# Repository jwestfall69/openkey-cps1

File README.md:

# openkey-cps1
---
* [Overview](#overview)
* [Project Status](#project-status)
* [Supported C Boards](#supported-c-boards)
* [CPS 1 Case](#cps-1-case)
* [Supported Games / B-XX Chips](#supported-games--b-xx-chips)
  * [CPS 1](#cps-1)
  * [CPS 1.5](#cps-15)
  * [B-XX](#b-xx)
* [Hardware](#hardware)
  * [PCB Manufacturing](#pcb-manufacturing)
  * [BOM](#bom)
  * [Assembly](#assembly)
    * [CPS 1](#cps-1-1)
    * [CPS 1.5](#cps-15-1)
* [Programming](#programming)
  * [Hardware](#hardware-1)
  * [Software](#software)
* [Installation](#installation)
  * [CPS 1](#cps-1-2)
  * [CPS 1.5](#cps-15-2)
  * [Reset Header (optional)](#reset-header-optional)
    * [Reset Capacitor Locations](#reset-capacitor-locations)
    * [Reset Signal Locations](#reset-signal-locations)
    * [Reset Cable](#reset-cable)
    * [Reset Delay Jumper](#reset-delay-jumper)
* [Reverting a modified C Board](#reverting-a-modified-c-board)

## Overview
This is an open source/hardware implementation of an on the fly CPS B-21 chip programmer that consists of a PCB that sits between CPS1/1.5 B and C boards.

Installed:<br>

This project is providing the same functionality as [Undamned's InfiniKey-CPS1](https://www.arcade-projects.com/threads/infinikey-cps1.8337/).  The lack of supply is what prompted me to make openkey-cps1.  If they ever end up coming back in stock please consider purchasing those to support [Undamned](https://www.arcade-projects.com/forums/temple-of-the-undamned.77/)'s work.

Details on *how* to program the CPS B-21 chip configuration can be found in [Eduardo Cruz](http://arcadehacker.blogspot.com/)'s [write up](http://arcadehacker.blogspot.com/2015/04/capcom-cps1-part-1.html) and [youtube video](https://www.youtube.com/watch?v=IBZc__9sM28).  Additional information is also comes from [cps2-reverse](https://gitlab.com/loic.petit/cps2-reverse) project which has details on the [CPS B-21](https://gitlab.com/loic.petit/cps2-reverse/-/tree/master/DLs/DL-0921) chip.

Details on *what* to program can be found in MAME's code for the [CPS1](https://github.com/mamedev/mame/blob/master/src/mame/capcom/cps1_v.cpp#L470).

## Project Status
**PCB:** Done

**Firmware:** Need to get untested games tested

**Documentation:** Done

## Supported C Boards
The following unmodified C Boards are supported

* [90630C-4](https://www.mvs-scans.com/index.php/CPS1_-_C_Board_90630C-4)
* [90631C-5](https://www.mvs-scans.com/index.php/CPS1_-_C_Board_90631C-5)
* [92641C-1](https://www.mvs-scans.com/index.php/CPS1_-_C_Board_92641C-1)

## CPS 1 Case
openkey-cps1 will not fit in the CPS 1 case.  As far as I know only Varith and Capcom World 2 came in a case.  You can still use openkey-cps1 to desuicide the C board.  Replace the battery then boot up the game with openkey-cps1 installed.  Verify it runs as expected, then power off, remove openkey-cps1 and reinstall the board in the case.

## Supported Games / B-XX Chips
openkey-cps1 supports either having a 5 position switch or using solder jumpers for picking what to program into the B-21 Chip.  For the switch, ensure the switches are fully set.  You should hear a click sound as you change the position.

 Below is a list of supported configurations/games and what switches/jumpers must be used for each.

### CPS 1
| Switch<br>12345 | Program ROM Labels | Game Name | Tested / Working |
|:---------------:|:------------------:|-----------|:--------------:|
| 00000 | CCE<br>CCJ<br>CCU<br> | Captain Commando | YES |
| 00001 | KDE<br>KDJ<br>KDU | The King of Dragons | |
| 00010 | KR_23E<br>KR_23J<br>KR_23U | Knights of the Round | YES |
| 00011 | Q5 | Capcom World 2 | YES |
| 00100 | QDU | Quiz & Dragons | YES |
| 00101 | RTE<br>RTJ<br>RTU | Three Wonders | YES |
| 00110 | VAE<br>VAJ<br>VAU | Varth | YES |

### CPS 1.5
| Switch<br>12345 | Program ROM Labels | Game Name | Tested / Working |
|:---------------:|:------------------:|-----------|:--------------:|
| 00111 | CDE<br>CDJ<br>CDT<br>CDU | Cadillacs & Dinosaurs | YES |
| 01000 | MBE<br>MBJ<br>MBU | Slam Masters / Muscle Bomber | YES |
| 01001 | MBDE<br>MBDJ | Muscle Bomber Duo | |
| 01010 | PSE<br>PSH<br>PSJ<br>PSU | Punisher | YES |
| 01011 | TK2E<br>TK2J<br>TK2U | Warriors of Fate | |

### B-XX
For B-XX chips prior to B-21 the configurations were hard coded into the chip.  Its possible to program the B-21 to mimic these older chips.

Some older B-XX boards will have the number stamped on instead of etched into the chip.  These stamped numbers maybe incorrect.  For example I have a final fight board that has 04 stamped on as the XX number.  Picking B-04 on openkey-cps1 didn't work.  After dumping the program roms I was able to determine it was the ffightua romset.   [Mame](https://github.com/mamedev/mame/blob/master/src/mame/capcom/cps1_v.cpp#L1754) shows this romset actually uses B-01.  Switching to B-01 made the game work.

| Switch<br>12345 |  B-XX  | Tested / Working |
|:---:|:------:|:---------------:|
| 01100 | B-01 | YES |
| 01101 | B-02 | |
| 01110 | B-03 | |
| 01111 | B-04 | YES |
| 10000 | B-05 | |
| 10001 | B-11 | YES |
| 10010 | B-12 | YES |
| 10011 | B-13 | YES |
| 10100 | B-14 | YES |
| 10101 | B-15 | |
| 10110 | B-16 | YES |
| 10111 | B-17 | YES |
| 11000 | B-18 | |
| 11001 | B-21 | YES |

## Hardware
### PCB Manufacturing
There are no special requirements for manufacturing.

I've been using [jlcpcb](https://jlcpcb.com/) for PCB manufacturing.  Just watch out that by default they will add an order number to the silk screen unless you tell them not to.

### BOM
| Quantity | Description | Part Number | DigiKey | Mouser | Notes |
|:----------:|-------------|-------------|---------|--------|-------|
| 1 | ATtiny404 20Mhz | ATTINY404-SSN | [ATTINY404-SSN-ND](https://www.digikey.com/en/products/detail/microchip-technology/ATTINY404-SSN/9947546) | [556-ATTINY404-SSNR](https://www.mouser.com/ProductDetail/Microchip-Technology-Atmel/ATTINY404-SSNR?qs=F5EMLAvA7IAEqD7Aw0z%252B9Q%3D%3D) | Other ATtiny tinyAVR 0/1/2-series models should be viable as well.  The code compiles to just under 1.5K in size, so any that have 2k or more of flash should work.  Just note I have only tested with 404s |
| 1 | 100nf / 0.1uf SMD Ceramic Capacitor 0805 Size | | | | |
| 1 | 5 Position Slide Switch | Würth Elektronik 416131160805 | [732-3855-2-ND](https://www.digikey.com/en/products/detail/w%C3%BCrth-elektronik/416131160805/3174531) | [710-416131160805](https://www.mouser.com/ProductDetail/Wurth-Elektronik/416131160805?qs=2kOmHSv6VfT1rqUsojuQog%3D%3D) | **Optional** not needed if using the solder jumpers to pick the game.
| 4 | CPS1: 2x20 Pin Male IDC connector<br>CPS1.5: 2x20pin Male Header (no shroud) | SBH11-PBPC-D20-ST-BK<br>N/A | [S9175-ND](https://www.digikey.com/en/products/detail/sullins-connector-solutions/SBH11-PBPC-D20-ST-BK/1990068)<br>[2x20 Pin Header](https://www.amazon.com/dp/B083DYVWDN?psc=1&ref=ppx_yo2ov_dt_b_product_details) | ?? | This is just a standard IDE male connector<br>This is just a normal 2x20 Pin header you might find for a PI's GPIO pins |
| 4 | 2x20 Pin Female socket | SFH11-PBPC-D20-ST-BK | [S9200-ND](https://www.digikey.com/en/products/detail/sullins-connector-solutions/SFH11-PBPC-D20-ST-BK/1990093) | ?? |  |

**IMPORTANT** For the 2x20 Pin Female socket, if you choose a different part, make sure you get ones that have the extra plastic on the edge as seen below.

The extra plastic prevents the connector from being inserted off-by-one.  An off-by-one insertion will cause a direct short to ground. This can cause catastrophic damage to your Game PCB if your power supply doesn't have short circuit protection.

Don't be fooled into thinking you don't need the extra plastic because you see the key. The bottom connector for example is too skinny for the key to actually prevent off-by-one insertion.  Ask me how I know ;)

### Assembly
#### CPS 1
Nothing special is needed when assembling a openkey-cps1 that will be used in a normal non-case'd CPS1 board.  Install SMD components first, then install the 40 pin male/female connectors.

#### CPS 1.5
Installing openkey-cps1 in a CPS 1.5 case is a tight fit height wise.  The pins that stick out of the C board are at the point of touching the top of the case.  If you are ok with this just use the 40 pin IDE style connectors.  Otherwise you can do the following.

To deal with this the best course of action is to only have raw pins for the male 40 pin connectors instead of ones with the plastic shroud.  This will allow the C board to sit flush with the openkey-cps1 board and reduce the height enough to not touch the top of the case.  Below is what has worked well for me, but there maybe better ways.

Some things to consider:
  * The normal pin length of a male pin is 6mm
  * The max pin height above the openkey-cps1 board should **not exceed 7mm**.  Any longer and the pin will bottom out on the female connector on the C Board.  This will cause the C board to not sit flush to the openkey-cps1 board and defeat the purpose of using raw pins.
  * You can't just install the normal 40pin IDE style connector then remove the shroud.  The resulting pin length ends up being 8mm.
  * You can't just install a normal 40 pin header and remove the plastic.  The resulting pin length ends up being 8mm.
  * The total length of metal pin on most headers is going to be 11.5mm
  * PCB thickness should be 1.6mm, which leave about 10mm worth of metal pin length we must deal with.

This method targets having 7mm above and 3mm below the openkey-cps1 board.  I've tried 6mm/4mm, but that 4mm is long enough there is risk it could hit/damage components on the B board.

You will want 4 normal 2x20 pin headers where the total metal length is 11.5mm.  Additionally you will want something you can use as a 1.5mm spacer.  I'm using the 2 black 24AWG wires in the picture below.

You will want to install 2 of the 2x20 pin header upside into board.  I would advise doing the 2 outer ones first. Put the 1.5mm spacer between the board and the plastic part of the connector as seen below.

Now flip the board over to the side we will be soldering.  It should look something like this.  

The length of the pins should be 3mm, which will mean 7mm on the top.

At this point I would tack 2 pins on each connector then verify spacing of the connectors looks good.  It should look something like this (with the spacer wires removed)

If you measure the pin lengths they should be right at 7mm.

Fully solder those 2 connectors.  Its extra importing you check your soldering that this point.  The next steps will involve removing the plastic part of the connectors which will make every pin independent and a pita to solder.

To protect the board I would put down some painters tape.  Additionally I use this [chip lifter](https://www.amazon.com/Wiha-27921-PicoFinish-Precision-Chiplifter/dp/B0875LSTD3/ref=sr_1_5)  as my pry tool. The grove makes it possible to get in between the pins to when prying up the plastic.

If you have a hot air station you can use it to heat (200C) up the plastic to make it easier to get off.  You will want to do the removable in a couple passes with your pry tool, lifting up the plastic a few mm per pass.

As you get the plastic higher up on the pins it can be helpful to add a spacer under you pry tool.  I'm just using a old prototype board.

Once you get both plastics off it should looks like this

Then you can go onto the middle 2 connectors.  You can bypass using the 1.5mm spacer on these.  Instead just put the connects in the PCB upside down as before, then flip PCB over as if you were going to solder them.  The already soldered connectors will hold the PCB 7mm off your table, which will mean your to be installed connectors will also be 7mm off your table.  Tack, verify and then fully solder.

Repeat the process to remove the plastic

When you are all done you should have this

Now do a test fit of the C board and it should be flush with the openkey-cps1 PCB

Install the SMD components and female 40 pin connectors.  This one was going on my Punisher board, so I just used the solder jumpers instead of installing the 5 position switch.

## Programming
The latest firmware will work on both revisions of openkey-cps1 hardware.

### Hardware
Programming is done with a UPDI programmer.  I've been using this one:

[Serial UPDI Programmer for ATmega 0-Series, or ATtiny 0-Series or 1-Series, or AVR DA or AVR DB](https://www.amazon.com/dp/B09X64YRLD?psc=1&ref=ppx_yo2ov_dt_b_product_details)

Note: This programmer (and likely others) has a switch for 3.3V and 5V.  Set it to 5V.

The openkey-cps1 programming port is setup so you can wedge the pins from the above programmer directly into them to programming.

Of course be sure you properly orient the board so the labeled pin/holes match up.  vcc to vcc, gnd to gnd, and updi to updi.

### Software
For software I've been using the [Arduino IDE](https://www.arduino.cc/en/software/) with [megaTinyCore](https://github.com/SpenceKonde/megaTinyCore), which adds support for tinyAVR 0/1/2-Series MCUs.

To install the megaTinyCore you, should just need to add http://drazzy.com/package_drazzy.com_index.json to "Additional Boards Manager URLs" in the settings for the Arduino IDE.

From there you need to configure the board/programming settings.  I've been using these:

**NOTE:** The "Startup Time" was adjusted from my previous picture of the settings, from 0ms to 1ms.  In testing I found when using a 0ms startup there is a small chance the ATtiny won't even execute any code.

## Installation
### CPS 1
Nothing really special here.  Use the dip switches or solder jumpers to pick your game/chip and put the openkey-cps1 board between your C and B boards.  The male/female connectors should prevent you from installing incorrectly.

### CPS 1.5
This is assuming you are using an openkey-cps1 board with the raw pin headers on top.  There is nothing preventing you from install the C board incorrectly.

Use the dip switches or solder jumpers to pick your game.

Verify you have the C board oriented the correct way as seen below.

The C board female connector will prevent you from installing it to high or low, but it will not prevent installation to the left or the right by one.

Check both sides of the female C board connector to verify you dont see any of the pins.

other side

If its off by one of the sides will look like this

### Reset Header (optional)
In openkey-cps1 hardware revision 2025-10-18 an optional reset header was added to allow hooking up openkey to the reset line of the A board.  Its **unlikley** you would need this and I would avoid using it.

Openkey-cps1 is dependent on being able to re-program on the B-21 chip while the cps1 board is in reset.  This is because 2 of the pins related to programming are part of the data bus used by the main CPU to talk to the B-21 chip.  If openkey-cps1 were to try and do any of its programming outside of reset it would cause a bus conflict with the main CPU also trying to use those 2 pins and programming will fail.

#### Reset Capacitor Locations
The length of time the cps1 board is in reset is highly dependent on the reset capacitor located on the A board.  If this capacitor is faulty or going bad it can greatly reduce the amount of time the board is in reset when power is applied.  Before trying to use the reset header on the openkey-cps1 I would first try replacing the reset capacitor.

**Long A Board:**<br>

**Short A Board:**<br>

On both boards its a 1uf/16V ceramic capacitor (higher voltages are ok).

#### Reset Signal Locations
The location provided for each A board type is a through hole.  I would advise installing a right angle header instead of directly soldering a wire.  This will make it easy to connect/disconnect the cable both on the A board and openkey-cps1.

**Long A Board:**<br>

**Long A Board Installed:**<br>

**Short A Board:**<br>

**Short A Board Installed:**<br>

#### Reset Cable
Once you've added the reset header on the A board, run a cable from it to pin 1 on the reset header of the openkey-cps1 as shown below.

Then install the C board onto openkey-cps1 as you normally would.

#### Reset Delay Jumper
With the reset cable hooked up, openkey-cps1 will hold the cps1 board in reset while its programming, then release when complete.  Pins 2 and 3 of the reset header on openkey-cps1 are a jumper that will cause openkey-cps1 to keep the cps1 board in reset longer.  When jumped the firmware will hold the cps1 board in reset for 1 second before and after programming.

**IMPORTANT**: If this jumper is jumped and the reset cable is not hooked up, programming will fail 100% of the time!

## Reverting a modified C Board
Its pretty common to find one of the required C boards as having been modified to disable using the programmable configuration.  This forces them to use their default configuration.

The tale tale sign of a modified C board are pins 45 and 46 will have cut traces (normally they go to ground) and a wire from them to some point on the C board that is supplying 5 volts.  For example

The way I normally revert them is to remove the wire, and then put a solder blob so that pins 45, 46, and 47 (ground) are bridged together.  This puts the board back in its original state with all 3 of those pins being tied to ground.

Here is a close up of the solder blob on the pins

You can also see where they had cut the traces for pins 45 and 46, which would normally connect to that ground plane to the right.

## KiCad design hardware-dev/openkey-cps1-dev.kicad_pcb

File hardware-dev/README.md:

# openkey-cps1-dev Hardware
This is a dev version of openkey-cps1 hardware that makes it possible to rapidly test firmware changes.  I'm mainly just including this in the repo so I don't use it.

**Top:**

**Bottom:**

As you can see its a bit taller then the non-dev version to allow being able to change the selected game and re-program the firmware while the board is plugged into a cps1 A-B-C stack.  The 2 diodes ensure that USB power can only goto the ATtiny and that cps1 board power doesn't goto the USB.

After programming the ATtiny you will want to disconnect it from USB and either power-on or powercycle the cps1 board.  This is to ensure power is fully removed from the ATtiny so it will boot up normally when cps1 power is applied.

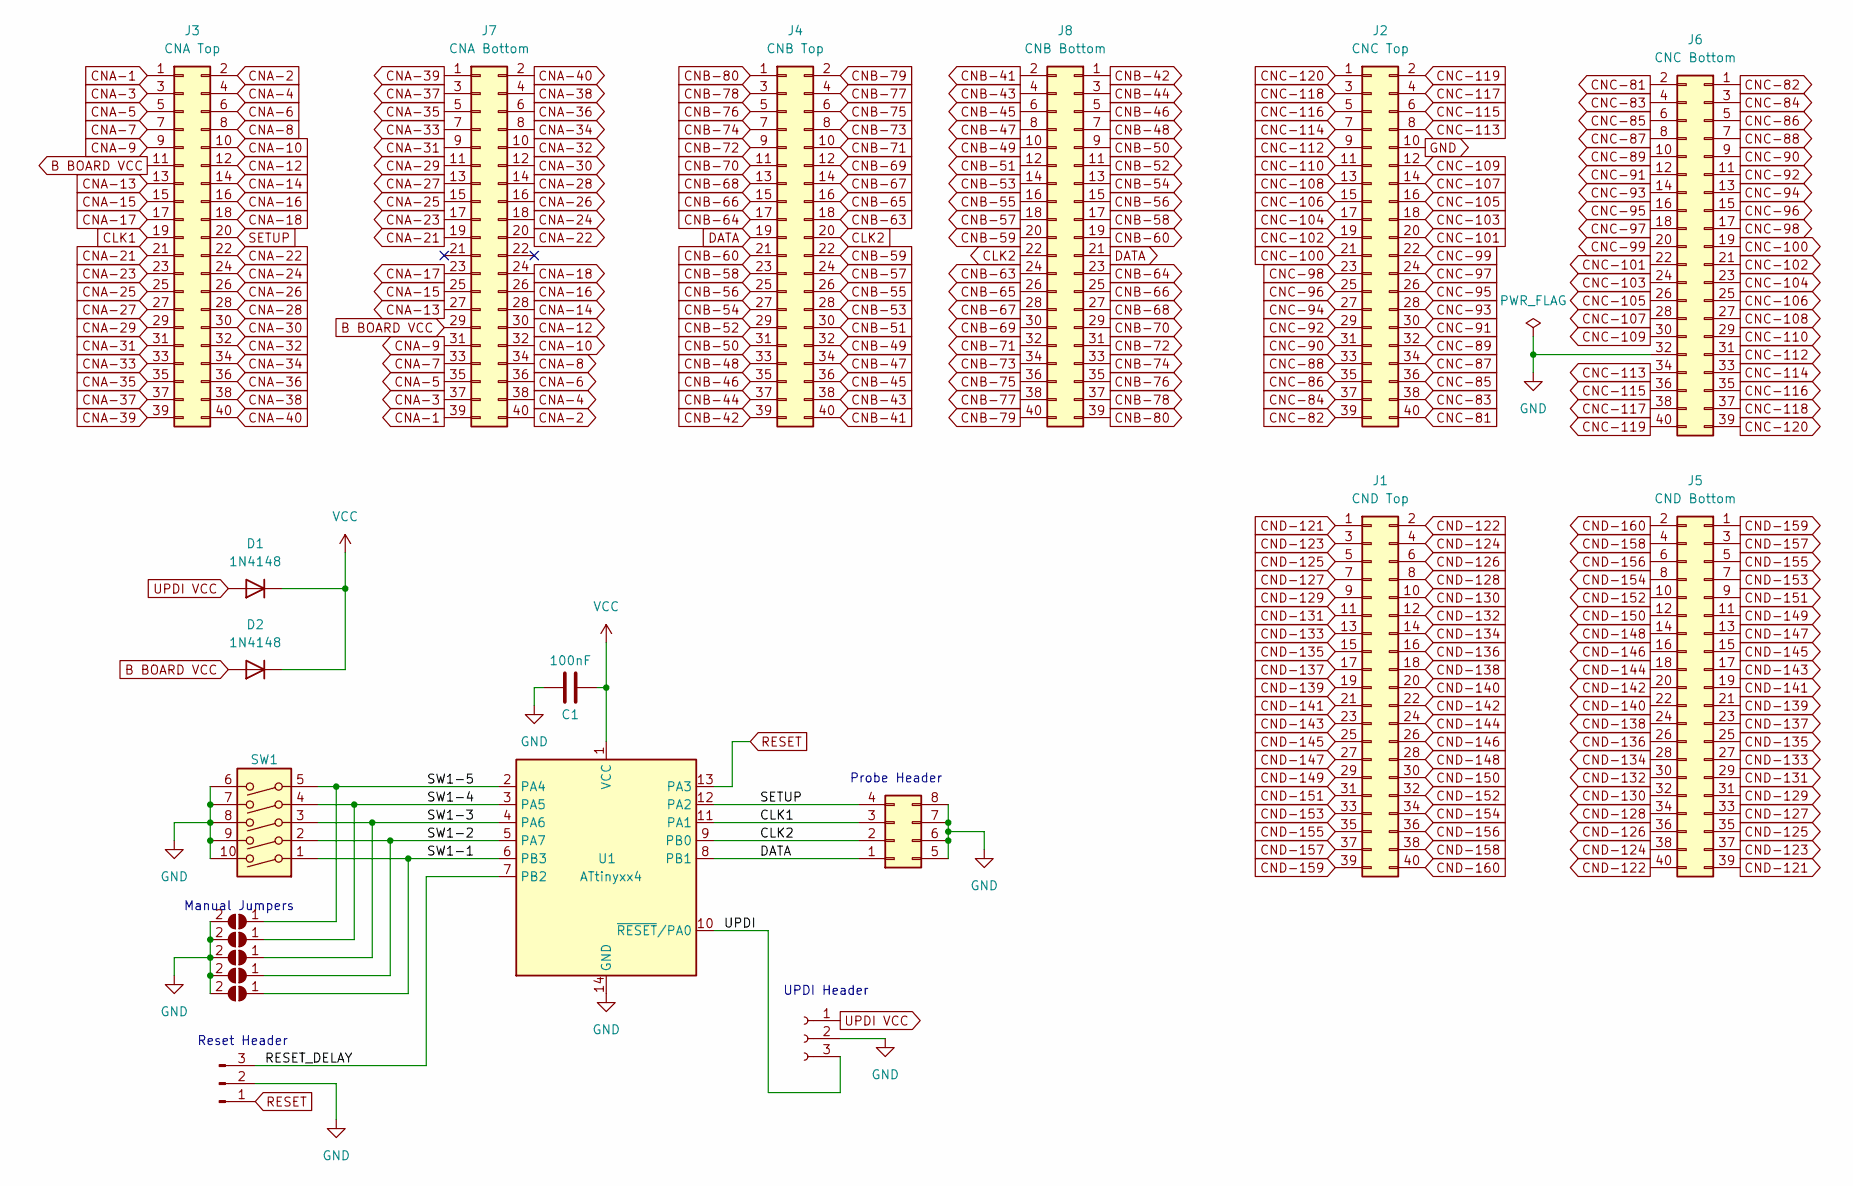
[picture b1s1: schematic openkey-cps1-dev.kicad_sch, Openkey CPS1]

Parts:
C1: 100nF; C_0805_2012Metric_Pad1.18x1.45mm_HandSolder
D1, D2: 1N4148; D_DO-35_SOD27_P7.62mm_Horizontal
J1: CND Top; IDC-Header_2x20_P2.54mm_Vertical_1.3mm
J2: CNC Top; IDC-Header_2x20_P2.54mm_Vertical_1.3mm
J3: CNA Top; IDC-Header_2x20_P2.54mm_Vertical_1.3mm
J4: CNB Top; IDC-Header_2x20_P2.54mm_Vertical_1.3mm
J5: CND Bottom; PinSocket_2x20_P2.54mm_Vertical_1.3mm
J6: CNC Bottom; PinSocket_2x20_P2.54mm_Vertical_1.3mm
J7: CNA Bottom; PinSocket_2x20_P2.54mm_Vertical_1.3mm
J8: CNB Bottom; PinSocket_2x20_P2.54mm_Vertical_1.3mm
J9: Conn_01x03_Female; PinHeader_1x03_P2.54mm_Vertical
J10: Conn_02x04_Top_Bottom; PinHeader_2x04_P2.54mm_Vertical
J12: Conn_01x03_Pin; PinHeader_1x03_P2.54mm_Vertical
JP1, JP2, JP3, JP4, JP5: SolderJumper_2_Open; SolderJumper-2_P1.3mm_Open_Pad1.0x0.6mm
SW1: SW_DIP_x05; SW_DIP_SPSTx05_Slide_Wurth_416131160805_W7.62mm_P1.27mm
U1: ATtinyxx4; SOIC-14_3.9x8.7mm_P1.27mm

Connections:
/RESET_DELAY: J12.3, U1.7 (PB2)
/SW1-1: JP5.1 (A), SW1.1, U1.6 (PB3)
/SW1-2: JP4.1 (A), SW1.2, U1.5 (PA7)
/SW1-3: JP3.1 (A), SW1.3, U1.4 (PA6)
/SW1-4: JP2.1 (A), SW1.4, U1.3 (PA5)
/SW1-5: JP1.1 (A), SW1.5, U1.2 (PA4)
/UPDI: J9.3, U1.10 (~RESET/PA0)
B BOARD VCC: D2.2 (A), J3.11, J7.29
CLK1: J3.19, J10.3, U1.11 (PA1)
CLK2: J4.20, J8.22, J10.2, U1.9 (PB0)
CNA-1: J3.1, J7.39
CNA-2: J3.2, J7.40
CNA-3: J3.3, J7.37
CNA-4: J3.4, J7.38
CNA-5: J3.5, J7.35
CNA-6: J3.6, J7.36
CNA-7: J3.7, J7.33
CNA-8: J3.8, J7.34
CNA-9: J3.9, J7.31
CNA-10: J3.10, J7.32
CNA-12: J3.12, J7.30
CNA-13: J3.13, J7.27
CNA-14: J3.14, J7.28
CNA-15: J3.15, J7.25
CNA-16: J3.16, J7.26
CNA-17: J3.17, J7.23
CNA-18: J3.18, J7.24
CNA-21: J3.21, J7.19
CNA-22: J3.22, J7.20
CNA-23: J3.23, J7.17
CNA-24: J3.24, J7.18
CNA-25: J3.25, J7.15
CNA-26: J3.26, J7.16
CNA-27: J3.27, J7.13
CNA-28: J3.28, J7.14
CNA-29: J3.29, J7.11
CNA-30: J3.30, J7.12
CNA-31: J3.31, J7.9
CNA-32: J3.32, J7.10
CNA-33: J3.33, J7.7
CNA-34: J3.34, J7.8
CNA-35: J3.35, J7.5
CNA-36: J3.36, J7.6
CNA-37: J3.37, J7.3
CNA-38: J3.38, J7.4
CNA-39: J3.39, J7.1
CNA-40: J3.40, J7.2
CNB-41: J4.40, J8.2
CNB-42: J4.39, J8.1
CNB-43: J4.38, J8.4
CNB-44: J4.37, J8.3
CNB-45: J4.36, J8.6
CNB-46: J4.35, J8.5
CNB-47: J4.34, J8.8
CNB-48: J4.33, J8.7
CNB-49: J4.32, J8.10
CNB-50: J4.31, J8.9
CNB-51: J4.30, J8.12
CNB-52: J4.29, J8.11
CNB-53: J4.28, J8.14
CNB-54: J4.27, J8.13
CNB-55: J4.26, J8.16
CNB-56: J4.25, J8.15
CNB-57: J4.24, J8.18
CNB-58: J4.23, J8.17
CNB-59: J4.22, J8.20
CNB-60: J4.21, J8.19
CNB-63: J4.18, J8.24
CNB-64: J4.17, J8.23
CNB-65: J4.16, J8.26
CNB-66: J4.15, J8.25
CNB-67: J4.14, J8.28
CNB-68: J4.13, J8.27
CNB-69: J4.12, J8.30
CNB-70: J4.11, J8.29
CNB-71: J4.10, J8.32
CNB-72: J4.9, J8.31
CNB-73: J4.8, J8.34
CNB-74: J4.7, J8.33
CNB-75: J4.6, J8.36
CNB-76: J4.5, J8.35
CNB-77: J4.4, J8.38
CNB-78: J4.3, J8.37
CNB-79: J4.2, J8.40
CNB-80: J4.1, J8.39
CNC-81: J2.40, J6.2
CNC-82: J2.39, J6.1
CNC-83: J2.38, J6.4
CNC-84: J2.37, J6.3
CNC-85: J2.36, J6.6
CNC-86: J2.35, J6.5
CNC-87: J2.34, J6.8
CNC-88: J2.33, J6.7
CNC-89: J2.32, J6.10
CNC-90: J2.31, J6.9
CNC-91: J2.30, J6.12
CNC-92: J2.29, J6.11
CNC-93: J2.28, J6.14
CNC-94: J2.27, J6.13
CNC-95: J2.26, J6.16
CNC-96: J2.25, J6.15
CNC-97: J2.24, J6.18
CNC-98: J2.23, J6.17
CNC-99: J2.22, J6.20
CNC-100: J2.21, J6.19
CNC-101: J2.20, J6.22
CNC-102: J2.19, J6.21
CNC-103: J2.18, J6.24
CNC-104: J2.17, J6.23
CNC-105: J2.16, J6.26
CNC-106: J2.15, J6.25
CNC-107: J2.14, J6.28
CNC-108: J2.13, J6.27
CNC-109: J2.12, J6.30
CNC-110: J2.11, J6.29
CNC-112: J2.9, J6.31
CNC-113: J2.8, J6.34
CNC-114: J2.7, J6.33
CNC-115: J2.6, J6.36
CNC-116: J2.5, J6.35
CNC-117: J2.4, J6.38
CNC-118: J2.3, J6.37
CNC-119: J2.2, J6.40
CNC-120: J2.1, J6.39
CND-121: J1.1, J5.39
CND-122: J1.2, J5.40
CND-123: J1.3, J5.37
CND-124: J1.4, J5.38
CND-125: J1.5, J5.35
CND-126: J1.6, J5.36
CND-127: J1.7, J5.33
CND-128: J1.8, J5.34
CND-129: J1.9, J5.31
CND-130: J1.10, J5.32
CND-131: J1.11, J5.29
CND-132: J1.12, J5.30
CND-133: J1.13, J5.27
CND-134: J1.14, J5.28
CND-135: J1.15, J5.25
CND-136: J1.16, J5.26
CND-137: J1.17, J5.23
CND-138: J1.18, J5.24
CND-139: J1.19, J5.21
CND-140: J1.20, J5.22
CND-141: J1.21, J5.19
CND-142: J1.22, J5.20
CND-143: J1.23, J5.17
CND-144: J1.24, J5.18
CND-145: J1.25, J5.15
CND-146: J1.26, J5.16
CND-147: J1.27, J5.13
CND-148: J1.28, J5.14
CND-149: J1.29, J5.11
CND-150: J1.30, J5.12
CND-151: J1.31, J5.9
CND-152: J1.32, J5.10
CND-153: J1.33, J5.7
CND-154: J1.34, J5.8
CND-155: J1.35, J5.5
CND-156: J1.36, J5.6
CND-157: J1.37, J5.3
CND-158: J1.38, J5.4
CND-159: J1.39, J5.1
CND-160: J1.40, J5.2
DATA: J4.19, J8.21, J10.1, U1.8 (PB1)
GND: C1.1, J2.10, J6.32, J9.2, J10.5, J10.6, J10.7, J10.8, J12.2, JP1.2 (B), JP2.2 (B), JP3.2 (B), JP4.2 (B), JP5.2 (B), SW1.6, SW1.7, SW1.8, SW1.9, SW1.10, U1.14 (GND)
RESET: J12.1, U1.13 (PA3)
SETUP: J3.20, J10.4, U1.12 (PA2)
UPDI VCC: D1.2 (A), J9.1
VCC: C1.2, D1.1 (K), D2.1 (K), U1.1 (VCC)

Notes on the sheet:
UPDI Header
Reset Header
Probe Header
Manual Jumpers

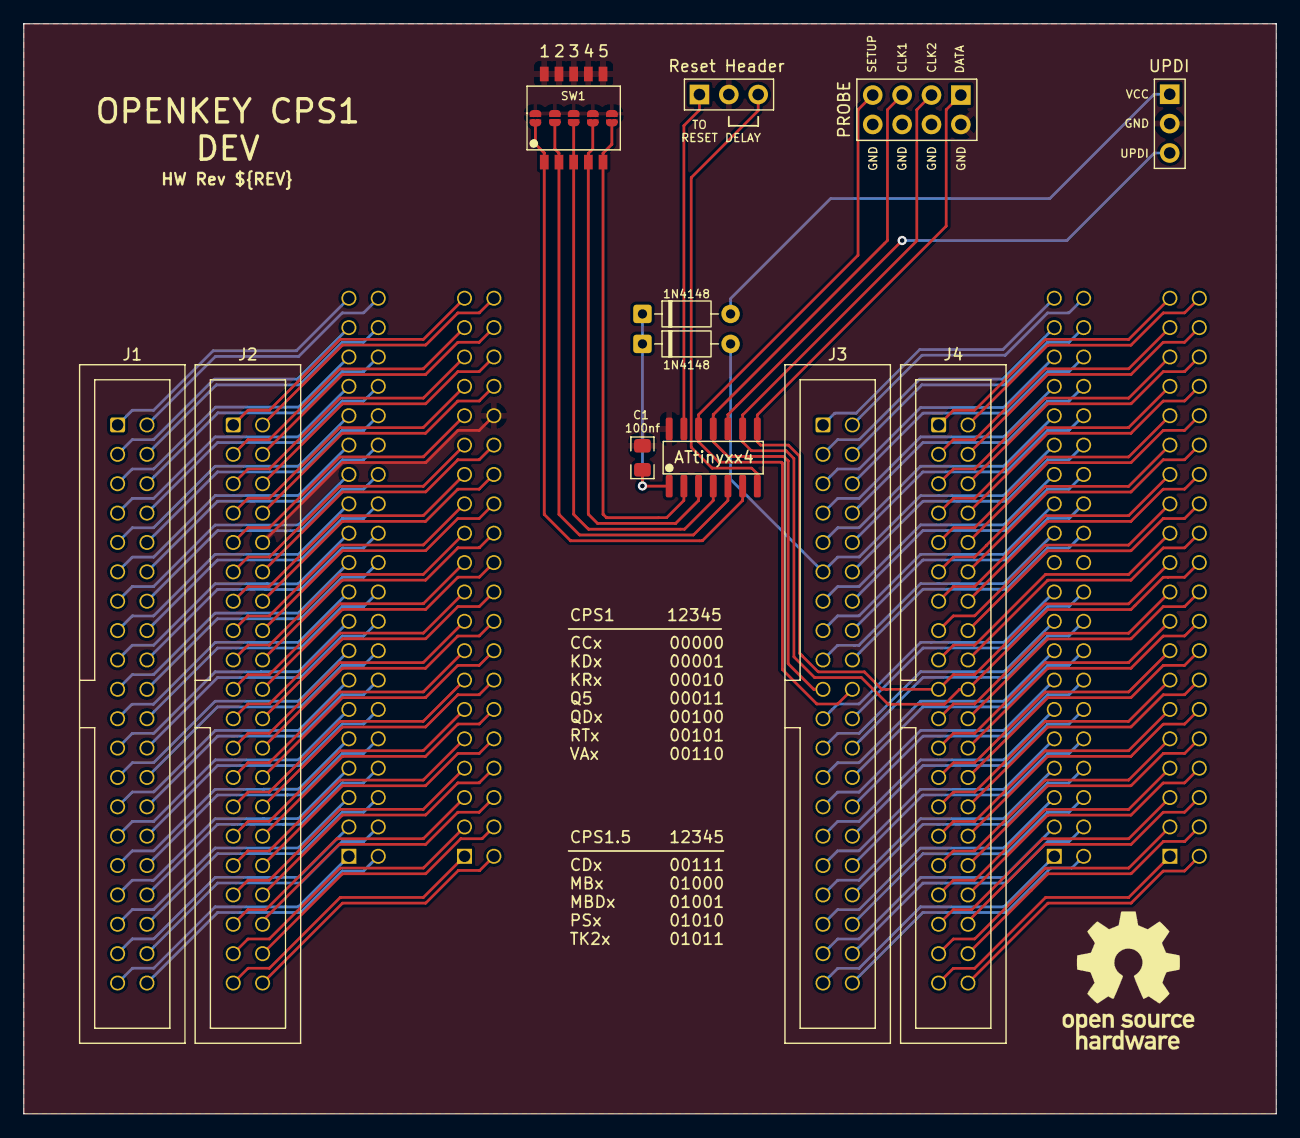
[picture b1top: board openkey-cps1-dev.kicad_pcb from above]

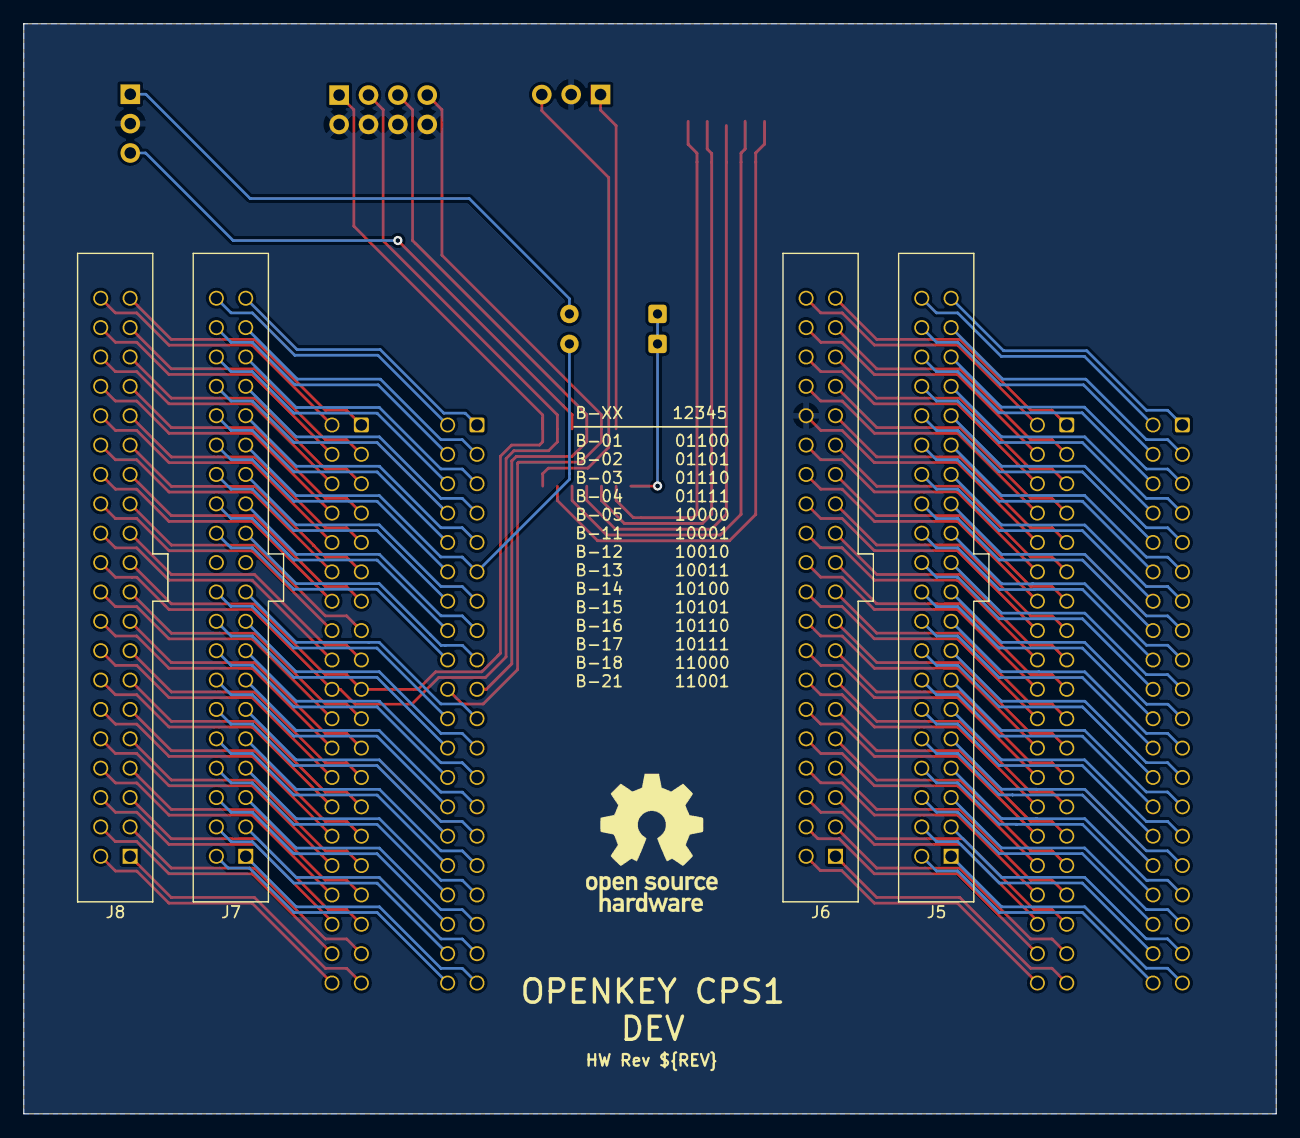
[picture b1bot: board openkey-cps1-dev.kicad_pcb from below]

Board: 2 copper layers, 108.3 x 94.3 mm, 21 parts (4 on the bottom side), 170 nets.

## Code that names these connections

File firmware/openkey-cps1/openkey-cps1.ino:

#include <avr/sleep.h>
#include "cps1-configs.h"

// PIN 8 (PIN_PB1) <=> CNB PIN 62
#define SET_DATA      PORTB.OUTSET = PIN1_bm
#define CLR_DATA      PORTB.OUTCLR = PIN1_bm

// PIN 9 (PIN_PB0) <=> CNB PIN 61
#define SET_CLK2      PORTB.OUTSET = PIN0_bm
#define CLR_CLK2      PORTB.OUTCLR = PIN0_bm

// PIN 10 (PIN_PA0) used for UPDI (ATtiny programming)

// PIN 11 (PIN_PA1) <=> CNA PIN 19
#define SET_CLK1      PORTA.OUTSET = PIN1_bm
#define CLR_CLK1      PORTA.OUTCLR = PIN1_bm

// PIN 12 (PIN_PA2) <=> CNA PIN 20
#define SET_SETUP     PORTA.OUTSET = PIN2_bm
#define CLR_SETUP     PORTA.OUTCLR = PIN2_bm

// PIN 13 (PIN_PA3) <=> "A" board reset line (optional)
#define SET_RESET     PORTA.OUTSET = PIN3_bm
#define CLR_RESET     PORTA.OUTCLR = PIN3_bm

// reset delay jumper is jumped (hw rev 2025-10-18)
#define RESET_DELAY !(PORTB.IN & 0b0000100)

// doing bit shifting takes a variable amount
// of time depending on the how far the shift
// is.  Using the below lookup table to try
// and keep a consistent clock period when
// sending data.
uint8_t masks[8] = {
  0x01, 0x02, 0x04, 0x08,
  0x10, 0x20, 0x40, 0x80,
};

void setup() {
  // set the programming pins as outputs
  PORTA.DIR = PIN1_bm | PIN2_bm | PIN3_bm;
  PORTB.DIR = PIN0_bm | PIN1_bm;

  // setup initial output states
  // https://www.youtube.com/watch?v=IBZc__9sM28&t=1196s
  CLR_RESET;
  SET_SETUP;
  CLR_CLK1;
  CLR_CLK2;
  CLR_DATA;

  // enable pull-ups on dsw / reset delay pins
  PORTA.PIN4CTRL |= PORT_PULLUPEN_bm;  // PIN 2 (PIN_PA4) <=> DSW5
  PORTA.PIN5CTRL |= PORT_PULLUPEN_bm;  // PIN 3 (PIN_PA5) <=> DSW4
  PORTA.PIN6CTRL |= PORT_PULLUPEN_bm;  // PIN 4 (PIN_PA6) <=> DSW3
  PORTA.PIN7CTRL |= PORT_PULLUPEN_bm;  // PIN 5 (PIN_PA7) <=> DSW2
  PORTB.PIN3CTRL |= PORT_PULLUPEN_bm;  // PIN 6 (PIN_PB3) <=> DSW1
  PORTB.PIN2CTRL |= PORT_PULLUPEN_bm;  // PIN 7 (PIN_PB2) <=> RESET_DELAY Jumper

  // Testing Notes:
  // - using a delay down near 500us will cause some games to report an
  //   addresss or ram error on boot
  // - going below that, programming stops working
  delayMicroseconds(1000);

  if(RESET_DELAY) {
    delay(1000);
  }

  // stage #1: clocks on clock #1
  // https://www.youtube.com/watch?v=IBZc__9sM28&t=1232s
  for(int i = 0;i < 4;i++) {
    SET_CLK1;
    CLR_CLK1;
  }

  // using updated info for stage #2/3
  // https://gitlab.com/loic.petit/cps2-reverse/-/blob/master/DLs/DL-0921/doc/security-scheme.md
  // stage #2: unlock key
  send_bits(0x5, 3);

  // stage #3: clocks on clock #2
  for(int i = 0;i < 15;i++) {
    SET_CLK2;
    CLR_CLK2;
  }

  uint8_t config_num = read_dsw();
  if(config_num >= CONFIG_MAX) {
    config_num = CONFIG_MAX - 1;
  }

  for(int i = 0; i < CONFIG_SIZE; i++) {
    send_bits(chip_configs[config_num][i], 8);
  }

  CLR_CLK1;
  CLR_CLK2;
  CLR_DATA;
  CLR_SETUP;

  if(RESET_DELAY) {
    delay(1000);
  }

  // NOTE: We dont connect pins 19/20 between the C and B boards.  These
  // pins are needed for programming but are normally tied to ground on
  // the B board.  In testing it appears the cps-b-21 chip has an internal
  // pull down for both, so it should be safe to disable pin output and
  // power down the ATtiny.

  // set all pins to be inputs
  PORTA.DIR = 0;
  PORTB.DIR = 0;

  // power down
  set_sleep_mode(SLEEP_MODE_PWR_DOWN);
  sleep_enable();
  sleep_cpu();
}

void loop() {
  while(1) {}
}

void send_bits(uint16_t data, int8_t num_bits) {
  num_bits--;
  while(num_bits >= 0) {
    uint32_t bit = data & masks[num_bits];
    if(bit) {
      SET_DATA;
    } else {
      CLR_DATA;
    }
    SET_CLK2;
    CLR_CLK2;
    num_bits--;
  }
}

// DSW1 = PB3 = bit4
// DSW2 = PA7 = bit3
// DSW3 = PA6 = bit2
// DSW4 = PA5 = bit1
// DSW5 = PA4 = bit0
uint8_t read_dsw() {
  uint8_t dsw = 0;
 
  // negate the bits since we are using
  // pull-ups so "on"s will be low
  uint8_t porta = PORTA.IN ^ 0xff;
  uint8_t portb = PORTB.IN ^ 0xff;

  dsw = porta >> 4;
  dsw = dsw | ((portb & 0b0001000) << 1);
  return dsw;
}

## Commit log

2022-10-11 initial checkin
2022-10-11 Add hardware
2022-10-11 Add firmware
2022-10-11 Tweak a couple ground traces
2022-10-12 Move firmware to a openkey-cps1 sub dir to keep arduino ide happy
2022-10-12 Add exported gerber directories to .gitignore
2022-10-27 Tweak vcc/gnd traces
2022-11-05 Initial Docs
2022-11-05 remove some commented out code related to a old hw rev
2022-11-05 Add TOC
2022-11-05 Doc update
2022-11-07 Tested update
2022-11-13 Docs: updates based on testing feedback from XtraSmiley
2022-11-13 Docs: Additional tested games thanks to XtraSmiley
2022-11-13 Docs: Add missing TOC element
2022-11-14 Update game config data to match up with ArcadeHacker's values
    Appears some of the values in mame don't work on real hardware.
2022-11-16 Docs: Add project status section
2022-11-16 Docs: Add project status and other minor changes
2022-11-17 Docs: programmer voltage switch
2022-11-25 Large refactor of firmware
    The human readable cps configs have been moved into its own c file
    (gen-cps1-configs.c). This will compile to its own binary and when run
    will generate cps1-configs.h. This file is included by the firmware and
    contains just the raw data that needed for programming each game/chip.
    The goal of this is to simplify/speed up programming process.
    Additional changes
2022-11-26 Docs Updates
    - add section on using raw pins for cps 1.5
    - add section on installation for cps 1.5 w/raw pins
    - notes about older B-XX having a stamped number that might be wrong
2022-11-30 Slam Masters and Quiz & Dragons retested by JammaJames2k
2022-12-11 Varth and B-04 tested
    Tested Varth with a varthjr conversion
    Tested B-04 with a varthu conversion
2022-12-13 knights and c&d retested, thanks to XtraSmiley
    varth also confirmed working for him
2025-10-26 Updated hardware/firmware that adds an optional reset header
    The optional reset header that can be used to hookup openkey-cps1
    to the A board's reset signal to allow openkey to control it. In
    general you shouldn't need this, but waited to make it an available
    option. More details are in the README.md
    The updated firmware is backwards compatible with the previous
    hardware revision.
2025-10-26 Add dev board
    This is the latest dev board that I use for testing firmware changes.
